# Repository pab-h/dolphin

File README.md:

# Dolphin

Velocimetro Digital para a minha bicicleta. Não cheguei a construí-lo por falta de material. Mas, quem quiser tentar, sinta-se livre. =)

> Para simular, foi utilizado o [Proteus 8](https://www.labcenter.com/)

## Requisitos

- [X] Medir a velocidade em Km/h;
- [X] Medir a distância percorrida;
- [X] Reiniciar a medida da velocidade (em caso de parada);
- [X] Reiniciar a distância percorrida;
- [X] Configurar o raio via software

## Materiais

- [Arduino Uno R3](https://docs.arduino.cc/hardware/uno-rev3/) 
- [Módulo TM1637 com Display 7 Segmentos 4 Dígitos](https://www.makerhero.com/produto/modulo-tm1637-com-display-7-segmentos-4-digitos/?srsltid=AfmBOoqLNAwazzRplnsqXKzoM1co3EbmQKjKahlsOt5L4xRWT-XB6TJF)
- [Magnetic Hall Effect Sensor (KY-024)](https://www.eletrogate.com/sensor-de-efeito-hall-ky-024?srsltid=AfmBOorNmNga4v0U0b5LsnoG5FFOnN1BOWNrU9AB9Dpqz0ndBUFFKoLm)
- [Push Button](https://www.autocorerobotica.com.br/botao-de-toque-6x6mm)
- [Resistores 10K](https://www.autocorerobotica.com.br/resistor-de-precisao-10k-1-4w-1)

## Multifunções nos botões

- Caso o botão esquerdo for pressionado por pelo menos 1 segundos, o sistema entra em modo de configuração. Se pressionado novamente por 1 segundos, o estado é revertido;

- No modo de configuração, é possível configurar o raio da roda. Botão esquerdo aumenta ao valor e o direito decrementa o valor;

- Se o botão direito for pressionado sem estar no estado de configuração, o hodometro é resetado;

## Esquema Elétrico e PCB

> Para a produção dessas imagens, foi-se utilizado o software [KiCad](https://www.kicad.org/)

## Pessoalmente,

Eu gostei muito de descobrir o [PlatformIo](https://platformio.org/). Minhas sinceras felicidades para os mantenedores desse projeto. Além disso, desenvolver a implementação de um botão multifunções foi devidamente interessante. Claro, isso foi uma bela surpresa para mim. Percebi que uma abordagem orientada a eventos e a objetos foi uma descoberta no desenvolvimento desse projeto.

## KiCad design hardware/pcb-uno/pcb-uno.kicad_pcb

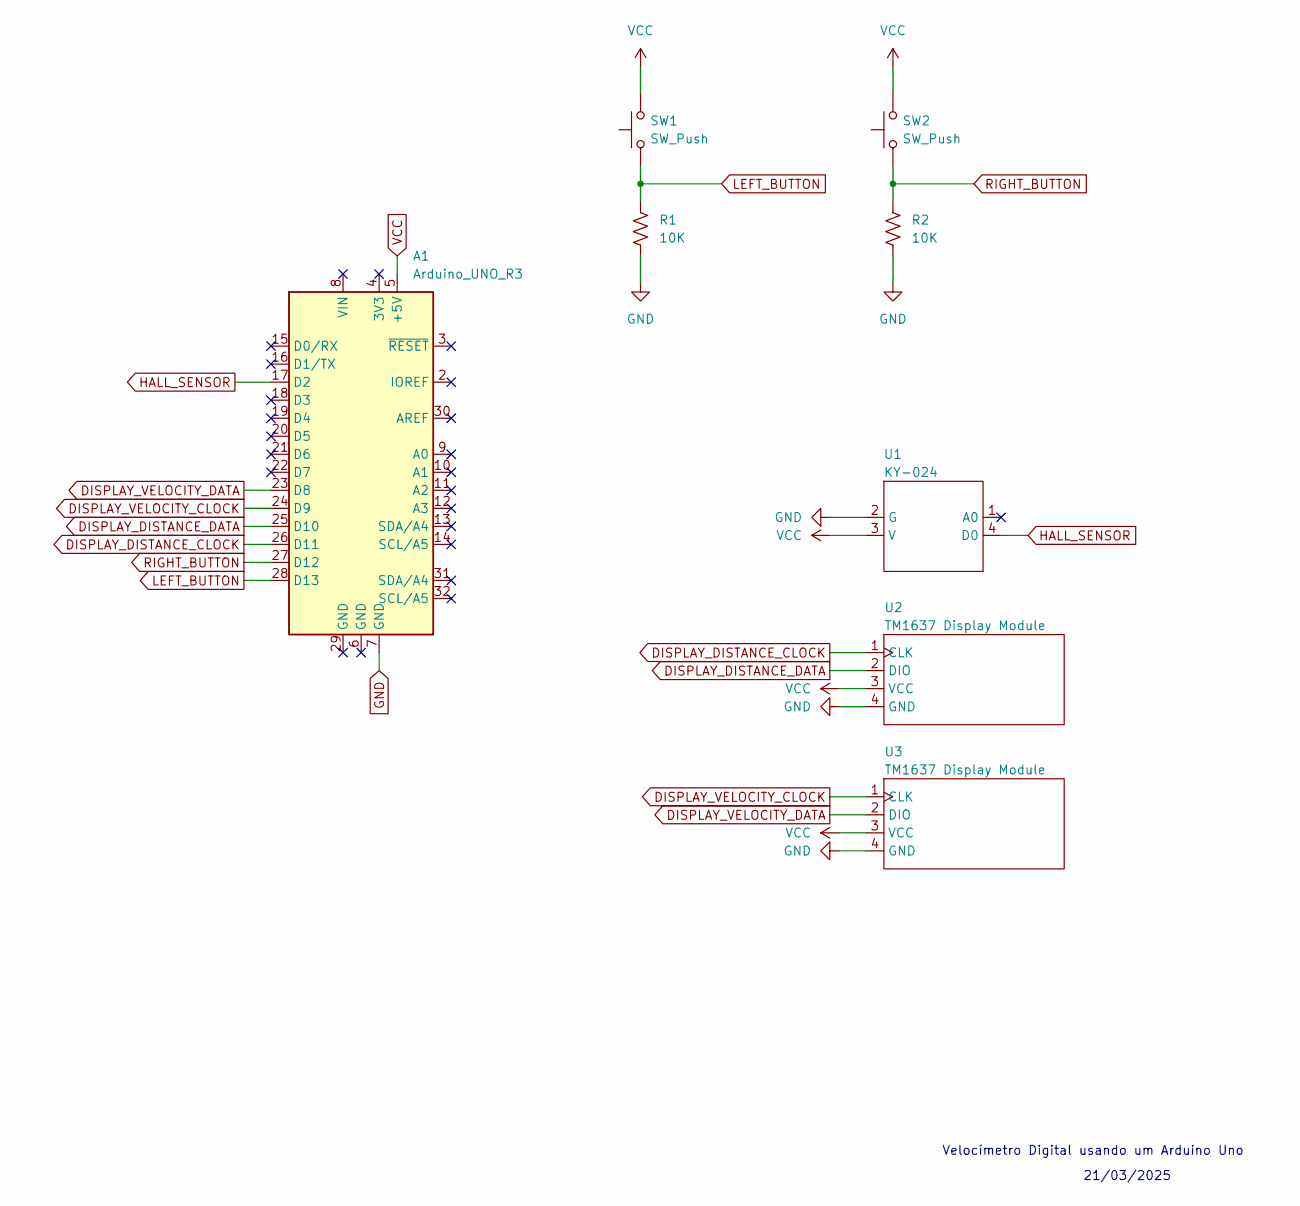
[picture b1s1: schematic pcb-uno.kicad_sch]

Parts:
A1: Arduino_UNO_R3
R1, R2: 10K; R_Axial_DIN0204_L3.6mm_D1.6mm_P5.08mm_Horizontal
SW1, SW2: SW_Push; SW_PUSH_6mm
U1: KY-024
U2, U3: TM1637 Display Module

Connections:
DISPLAY_DISTANCE_CLOCK: A1.26 (D11), U2.1 (CLK)
DISPLAY_DISTANCE_DATA: A1.25 (D10), U2.2 (DIO)
DISPLAY_VELOCITY_CLOCK: A1.24 (D9), U3.1 (CLK)
DISPLAY_VELOCITY_DATA: A1.23 (D8), U3.2 (DIO)
GND: A1.7 (GND), R1.2, R2.2, U1.2 (G), U2.4 (GND), U3.4 (GND)
HALL_SENSOR: A1.17 (D2), U1.4 (D0)
LEFT_BUTTON: A1.28 (D13), R1.1, SW1.1
RIGHT_BUTTON: A1.27 (D12), R2.1, SW2.1
VCC: A1.5 (+5V), SW1.2, SW2.2, U1.3 (V), U2.3 (VCC), U3.3 (VCC)

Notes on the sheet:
Velocímetro Digital usando um Arduino Uno
21/03/2025

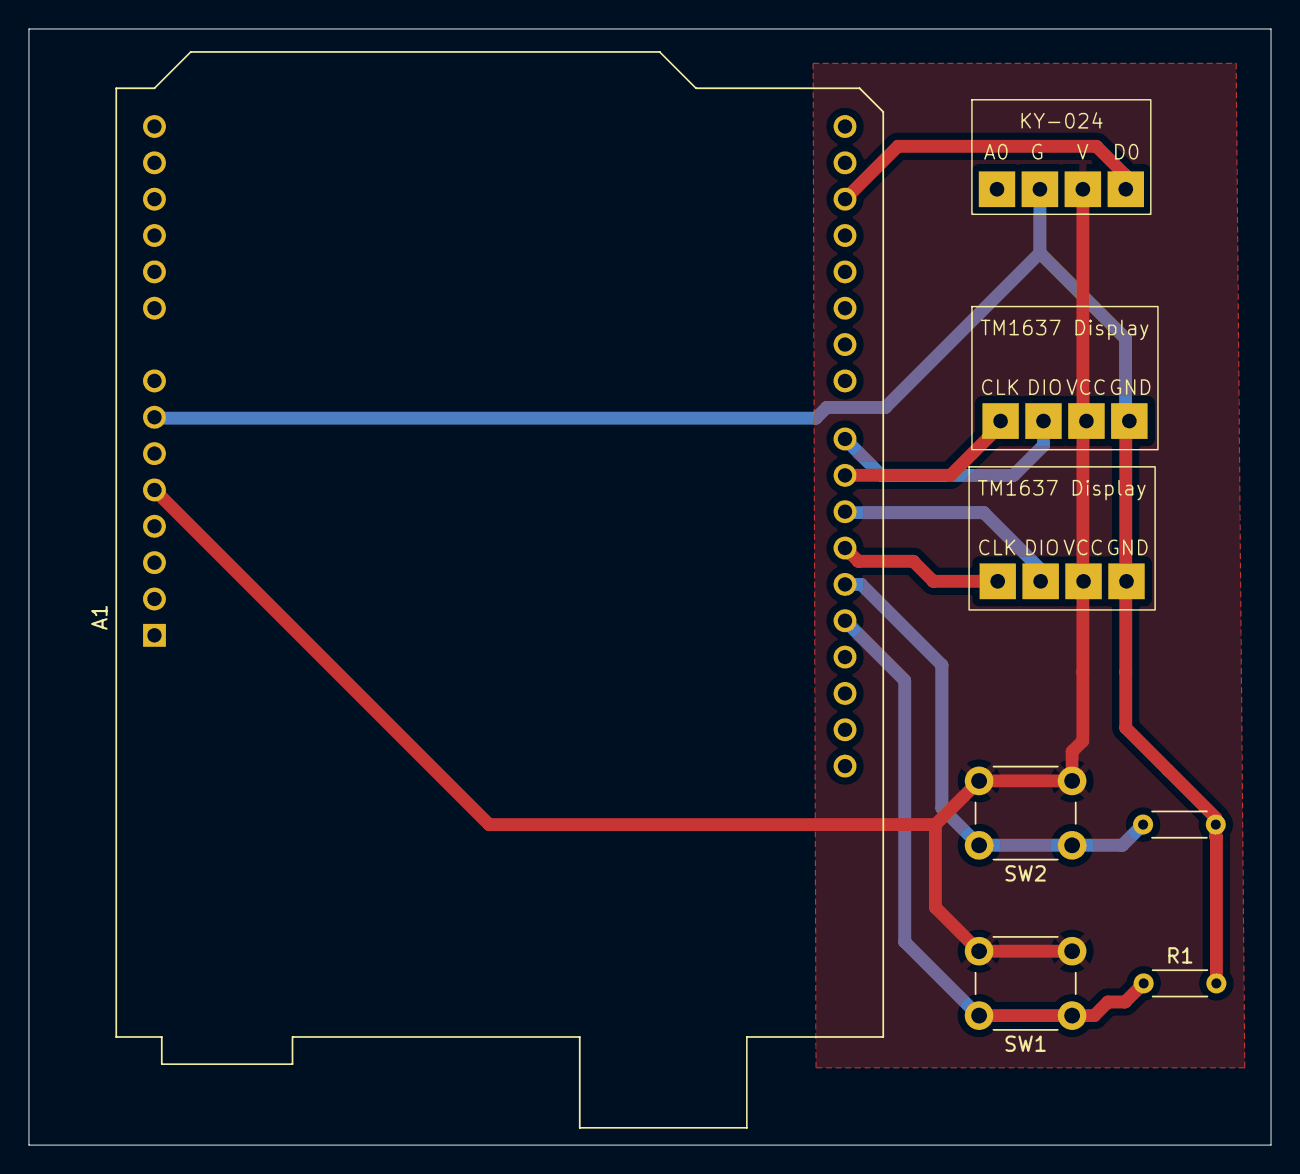
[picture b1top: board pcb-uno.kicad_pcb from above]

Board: 2 copper layers, 86.8 x 78.0 mm, 8 parts (0 on the bottom side), 9 nets.

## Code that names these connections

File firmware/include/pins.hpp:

#ifndef PINS_HEADER

#define PINS_HEADER

#include <Arduino.h>

#define LEFT_BUTTON_PIN  13
#define RIGHT_BUTTON_PIN 12

#define DISPLAY_DISTANCE_CLOCK_PIN 11
#define DISPLAY_DISTANCE_DATA_PIN  10

#define DISPLAY_VELOCITY_CLOCK_PIN 9
#define DISPLAY_VELOCITY_DATA_PIN  8

#define HALL_SENSOR_PIN 2

#endif

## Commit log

2025-03-07 feat: esquemático do hardware usando o Proteus 8 para a simulação
2025-03-07 feat: Configuração da Platformio
2025-03-07 feat: mapeamento de hardware
2025-03-07 feat: configuração dos pinos
2025-03-09 feat: arquivo de configurações
2025-03-09 feat: constantes de conversão
2025-03-09 feat: sensor hall
2025-03-09 feat: mudança nos pinos para otimizar as interrupções
2025-03-09 feat: o velocimetro
2025-03-09 feat: implementação do sensor hall
2025-03-09 faet: uso do velocimetro
2025-03-09 feat: mudança na ordem dos pinos
2025-03-10 feat: tempo de reset do odometro
2025-03-10 feat: odometro
2025-03-10 refactor: removendo volatile não utilizados
2025-03-10 feat: sem interrupção durante o calculo da velocidade
2025-03-10 fix: calculando os parametros dentro da interrupção para tentar mitigar o erro #5
2025-03-10 fix: por algum motivo, não desabilitar as interrupções faz o código responder melhor ao sensor sendo simulado por um botão
2025-03-10 feat: biblioteca para TM1637
2025-03-10 feat: sensor hall na pasta de sensores
2025-03-10 feat: odometro e velocimentro na pasta dos medidores
2025-03-10 cleanup: removendo import não utilizados
2025-03-10 feat: display de distância
2025-03-10 feat: display de velocidade
2025-03-10 feat: atualizando os displays a cada 500ms
2025-03-10 feat: utilizando um pulso de clock para simular o sensor hall
2025-03-15 feat: limiares para click e pressionar no botão
2025-03-15 refactor: autismo
2025-03-15 fix: o hodometro não deve ser resetado sem que o usuário queira
2025-03-15 refactor: limitar de reset no arquivo de configurações
2025-03-15 refactor: tipo mais adequado para o número do pino
2025-03-15 feat: Classe PushButton - lidar com clicks - lidar com pressionar o botão por 1 segundo (ou mais)
2025-03-17 feat: código base para a escrita do raio na EEPROM
2025-03-18 feat: RADIUS_EEPROM_ADDRESS
2025-03-18 feat: configuração do raio no construtor
2025-03-18 refactor: nome apropriado para o atributo no construdor do hodometro
2025-03-18 feat: classe que representa o sistema
2025-03-19 refactor: casting explícito
2025-03-19 refactor: tipo mais adquado para o número dos pinos
2025-03-19 feat: display de configuração
2025-03-19 feat: botão de resertar o hodometro
2025-03-25 feat: PCB
2025-03-25 docs: documentação básica do projeto
